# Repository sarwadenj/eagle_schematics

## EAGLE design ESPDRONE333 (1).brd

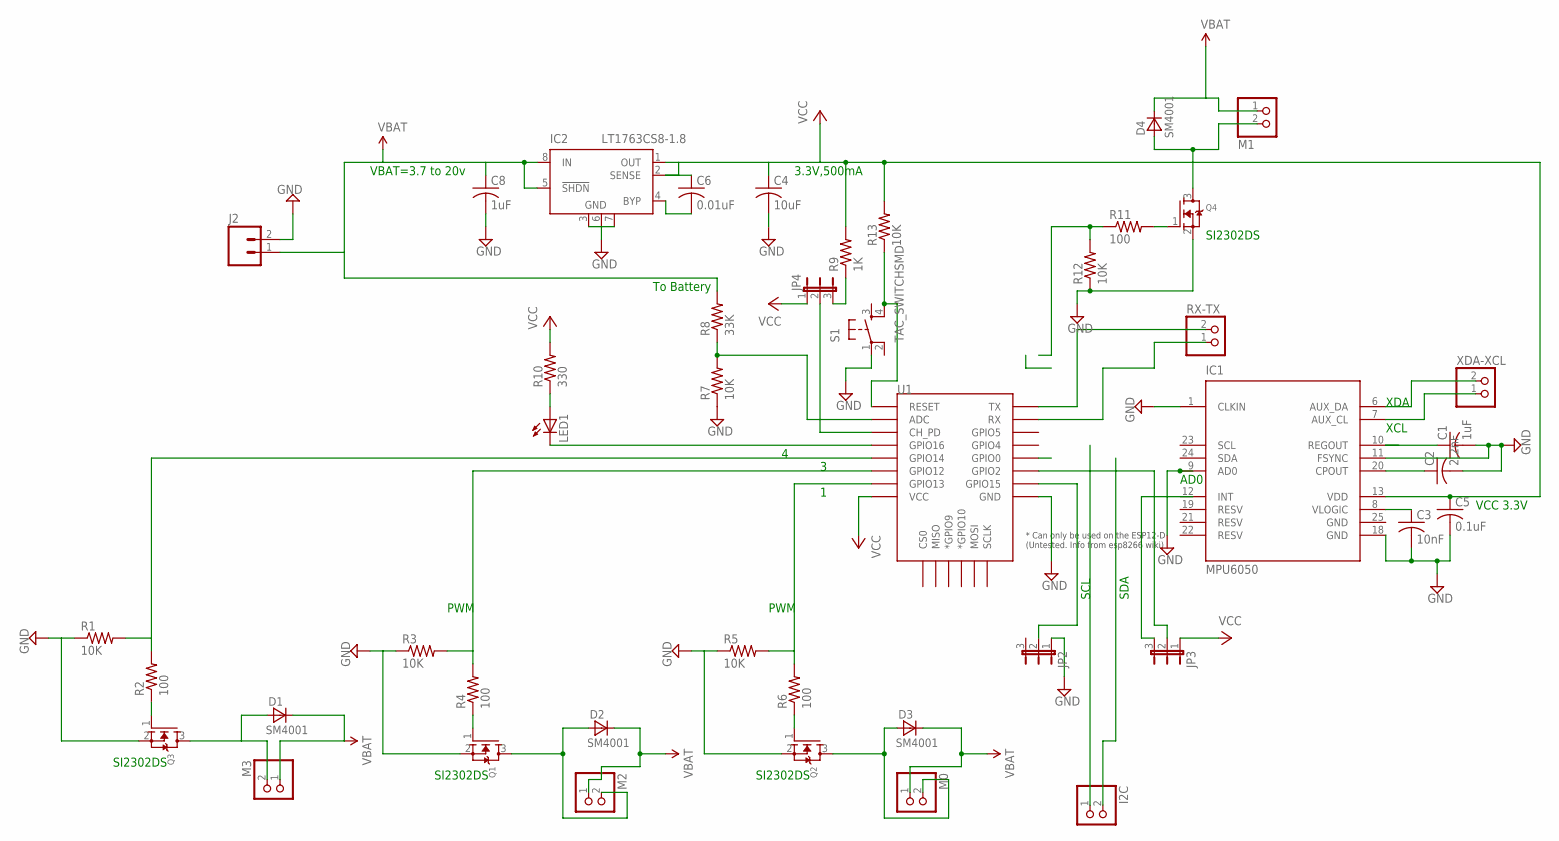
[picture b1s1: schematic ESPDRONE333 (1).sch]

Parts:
C1: 1uF; C1206K
C2: 2.2nF; C0603
C3: 10nF; C0603
C4: 10uF; C1608
C5: 0.1uF; C0603
C6: 0.01uF; C0603
C8: 1uF; C1608
D1, D2, D3, D4: SM4001; MELF-MLL41
I2C: JST_2PIN-SMT; JST-PH-2-SMT
IC1: MPU6050; QFN50P400X400X95-25T265X275N
IC2: LT1763CS8-1.8; SOIC8
J2: M02JST-PTH-2; JST-2-PTH
JP2, JP3, JP4: JP2E; JP2
LED1: LED; SMARTLED-TTW
M0, M1, M2, M3: JST_2PIN-SMT; JST-PH-2-SMT
Q1, Q2, Q3, Q4: MOSFET-NREFLOW; SOT23
R1, R3, R5, R7, R12, R13: 10K; R0603
R2, R4, R6, R11: 100; R0603
R8: 33K; R0603
R9: 1K; R0603
R10: 330; R0603
RX-TX: JST_2PIN-SMT; JST-PH-2-SMT
S1: TAC_SWITCHSMD; TACTILE-SWITCH-SMD
U1: ESP12ESMD; ESP12E-SMD
XDA-XCL: JST_2PIN-SMT; JST-PH-2-SMT

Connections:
GND: C1.2, C2.2, C3.2, C4.2, C5.2, C8.2, IC1.1 (CLKIN), IC1.9 (AD0), IC1.11 (FSYNC), IC1.18 (GND), IC1.25 (GND), IC2.3 (GND), IC2.6 (GND), IC2.7 (GND), J2.2, JP2.1, Q1.2 (S), Q2.2 (S), Q3.2 (S), Q4.2 (S), R1.1, R3.1, R5.1, R7.1, R12.1, S1.1, U1.GND
I2C: I2C.2 (1)
unnamed: R13.1, S1.4, U1.RESET
unnamed: R11.1, R12.2
unnamed: C1.1, IC1.10 (REGOUT)
unnamed: IC1.7 (AUX_CL), XDA-XCL.1 (2)
unnamed: C2.1, IC1.20 (CPOUT)
unnamed: JP3.2, U1.GPIO2
unnamed: C3.1, IC1.8 (VLOGIC)
unnamed: Q3.1 (G), R2.1
unnamed: D1.A, M3.2 (1), Q3.3 (D)
unnamed: R1.2, R2.2, U1.GPIO14
unnamed: R7.2, R8.1, U1.ADC
unnamed: Q4.1 (G), R11.2
unnamed: D2.A, M2.2 (1), Q1.3 (D)
unnamed: R3.2, R4.2, U1.GPIO12
unnamed: RX-TX.1 (2), U1.RXD0 (RX)
unnamed: Q1.1 (G), R4.1
unnamed: Q2.1 (G), R6.1
unnamed: LED1.A@1 (A), R10.1
unnamed: JP4.3, R9.1
unnamed: R5.2, R6.2, U1.GPIO13
unnamed: D3.A, M0.2 (1), Q2.3 (D)
unnamed: JP2.2, U1.GPIO15
unnamed: D4.A, M1.2 (1), Q4.3 (D)
unnamed: JP4.2, U1.CH_PD
unnamed: LED1.C@1 (C), U1.GPIO16
unnamed: C6.2, IC2.4 (BYP)
VCC: C4.1, C5.1, C6.1, C8.1, D1.C, D2.C, D3.C, D4.C, IC1.13 (VDD), IC2.1 (OUT), IC2.2 (SENSE), IC2.5 (!SHDN), IC2.8 (IN), J2.1, JP3.1, JP4.1, M0.1 (2), M1.1 (2), M2.1 (2), M3.1 (2), R8.2, R9.2, R10.2, R13.2, U1.VCC
VCC1: RX-TX.2 (1), U1.TXD0 (TX)
VCC2: IC1.6 (AUX_DA), XDA-XCL.2 (1)

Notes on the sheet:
XDA
XCL
AD0
VCC 3.3V
SDA
SCL
SI2302DS
PWM
To Battery
3.3V,500mA
VBAT=3.7 to 20v

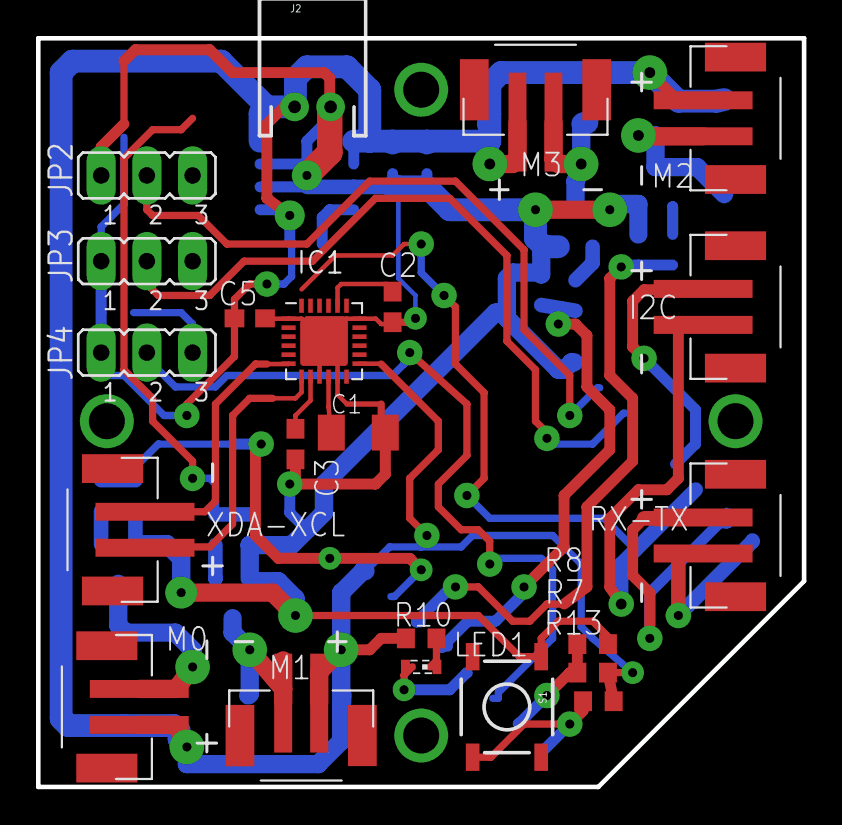
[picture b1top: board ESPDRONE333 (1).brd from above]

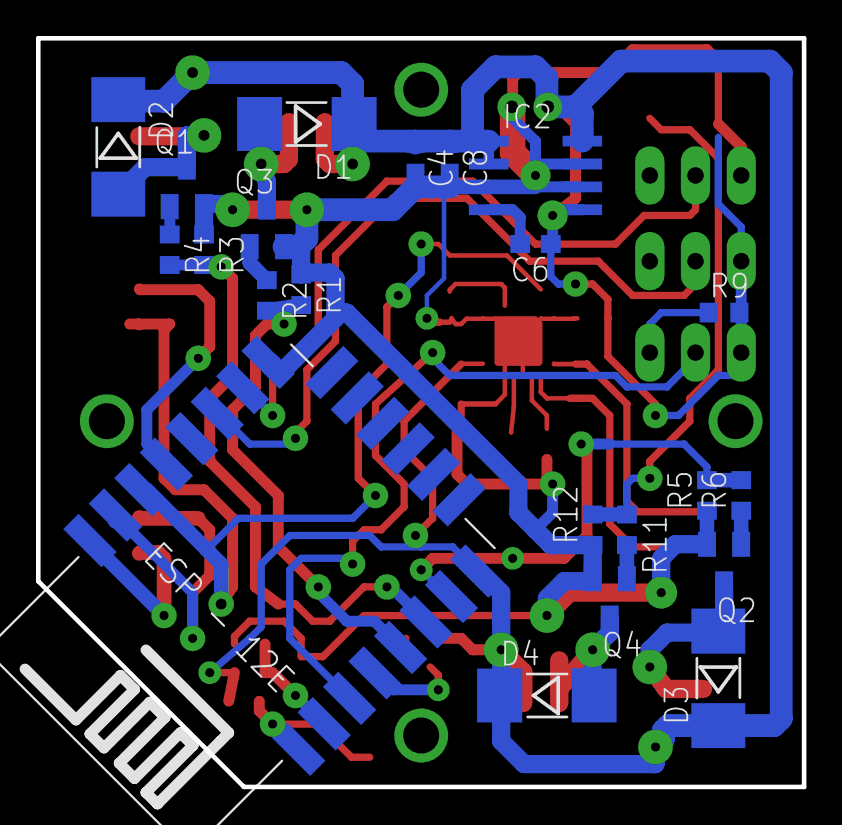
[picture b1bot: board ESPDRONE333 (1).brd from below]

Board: 2 copper layers, 42.5 x 41.6 mm, 44 parts (22 on the bottom side), 30 nets.

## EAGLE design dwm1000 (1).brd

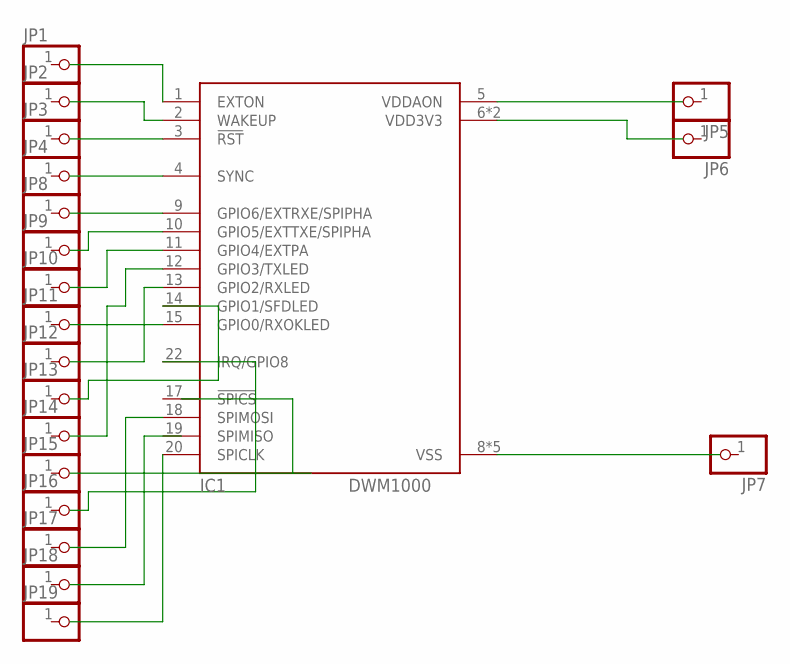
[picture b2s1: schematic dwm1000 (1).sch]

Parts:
IC1: DWM1000
JP1, JP2, JP3, JP4, JP5, JP6, JP7, JP8, JP9, JP10, JP11, JP12, JP13, JP14, JP15, JP16, JP17, JP18, JP19: PINHD-1X1_2.00; 1X01M

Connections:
unnamed: IC1.6 (VDD3V3), IC1.7 (VDD3V3)
unnamed: IC1.8 (VSS), IC1.16 (VSS), IC1.21 (VSS), IC1.23 (VSS), IC1.24 (VSS)

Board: 2 copper layers, 20 parts (0 on the bottom side), 2 nets, no tracks yet.

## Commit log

2017-09-05 :confetti_ball: Added .gitattributes & .gitignore files

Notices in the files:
parts and their libraries:
SparkFun-Connectors: Licensing: Creative Commons ShareAlike 4.0 International - https://creativecommons.org/licenses/by-sa/4.0
